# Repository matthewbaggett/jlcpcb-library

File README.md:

JLCPCB Autogenerated parts library
==================================

JLCPCB kindly provides a nice spreadsheet of parts available for their PCBA service.

I thought it'd be useful to turn that into an eaglecad parts library.

To maximise its usefulness, I've done a few other things:

 * Copied Sparkfuns fabulous Power Symbols library
 * Copied CAM job, Desirn Rules file & ULPs from https://github.com/oxullo/jlcpcb-eagle
 
## TODO List:
 * Fix non-trivial packages (multipin ICs)
 * Write Guide on how to export for JLCPCB:
   * Layout guidelines
   * Part picking
   * CAM exporting
   * Running jlcpcb_smta_exporter.ulp to get BOM and placement.
 * Dockerise this tool
 * Create github actions to run on a schedule.
 * Add github actions linting.
 * Proceedurally generate power symbols from a list of power rails

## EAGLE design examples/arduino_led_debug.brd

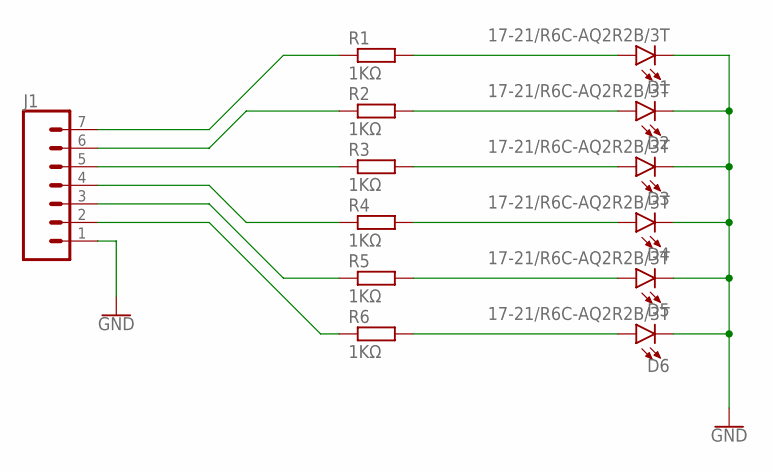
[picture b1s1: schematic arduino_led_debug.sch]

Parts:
D1, D2, D3, D4, D5, D6: 17-21/R6C-AQ2R2B/3T; LED_0805
J1: CONN_07LOCK; 1X07_LOCK
R1, R2, R3, R4, R5, R6: 1KΩ; RESISTOR_0402

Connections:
GND: D1.C, D2.C, D3.C, D4.C, D5.C, D6.C, J1.1
unnamed: D1.A, R1.1 (2)
unnamed: D2.A, R2.1 (2)
unnamed: D3.A, R3.1 (2)
unnamed: J1.7, R1.2 (1)
unnamed: D4.A, R4.1 (2)
unnamed: J1.2, R6.2 (1)
unnamed: J1.3, R5.2 (1)
unnamed: J1.4, R4.2 (1)
unnamed: J1.5, R3.2 (1)
unnamed: J1.6, R2.2 (1)
unnamed: D5.A, R5.1 (2)
unnamed: D6.A, R6.1 (2)

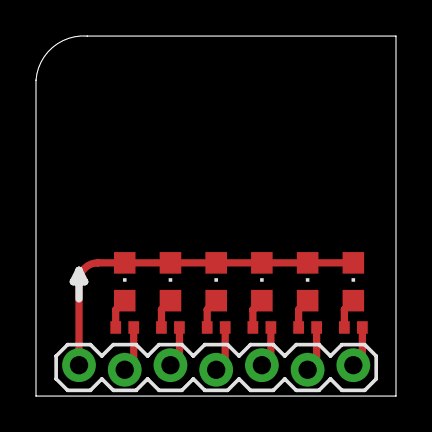
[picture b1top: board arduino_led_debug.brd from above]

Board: 2 copper layers, 20.0 x 20.0 mm, 13 parts (0 on the bottom side), 13 nets.

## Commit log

2020-03-31 Initial commit - Reads in the jlcpcb spreadsheet.
2020-04-05 Progress so far
2020-04-05 Fix up deps.
2020-04-05 First loadable libraries.
2020-04-05 More loadable libraries.
2020-04-05 Add more packages.
2020-04-05 More items.
2020-04-05 More parts. More documentation.
2020-04-10 Copied in some assets.
2020-04-10 Adding the skeleton of an example board project.
2020-04-11 Improving library. Still no real LED library! Added example project to test ULPs against.
2020-04-12 Shrank the label mess for 0402 - No value, just name.
2020-04-13 Updated Pins and Grid data.
2020-04-13 SM4007PL
2020-04-13 Working CH340g, but not programatically :thinking:
2020-04-13 IC_CH340G bits
2020-04-13 Device name strategy change.
2020-04-13 Now generates wonkey ICs
2020-04-13 rename
2020-10-13 Revise 0402 cap
2020-10-13 Minor parts changes
2020-10-13 Temporarilly supress a warning
2020-10-13 Add interop polyfills and updates
2020-10-15 Fix device set name generation. Regenerated libraries.
2021-06-29 Bump league/flysystem from 1.0.66 to 1.1.4
    Bumps [league/flysystem](https://github.com/thephpleague/flysystem) from 1.0.66 to 1.1.4.
    - [Release notes](https://github.com/thephpleague/flysystem/releases)
    - [Changelog](https://github.com/thephpleague/flysystem/blob/2.x/CHANGELOG.md)
    - [Commits](https://github.com/thephpleague/flysystem/compare/1.0.66...1.1.4)
    ---
    updated-dependencies:
2022-05-25 Bump guzzlehttp/guzzle from 6.5.2 to 6.5.6
    Bumps [guzzlehttp/guzzle](https://github.com/guzzle/guzzle) from 6.5.2 to 6.5.6.
    - [Release notes](https://github.com/guzzle/guzzle/releases)
    - [Changelog](https://github.com/guzzle/guzzle/blob/6.5.6/CHANGELOG.md)
    - [Commits](https://github.com/guzzle/guzzle/compare/6.5.2...6.5.6)
    ---
    updated-dependencies:
2022-06-10 Bump guzzlehttp/guzzle from 6.5.2 to 6.5.7
    Bumps [guzzlehttp/guzzle](https://github.com/guzzle/guzzle) from 6.5.2 to 6.5.7.
    - [Release notes](https://github.com/guzzle/guzzle/releases)
    - [Changelog](https://github.com/guzzle/guzzle/blob/6.5.7/CHANGELOG.md)
    - [Commits](https://github.com/guzzle/guzzle/compare/6.5.2...6.5.7)
    ---
    updated-dependencies:
2022-06-21 Bump guzzlehttp/guzzle from 6.5.2 to 6.5.8
    Bumps [guzzlehttp/guzzle](https://github.com/guzzle/guzzle) from 6.5.2 to 6.5.8.
    - [Release notes](https://github.com/guzzle/guzzle/releases)
    - [Changelog](https://github.com/guzzle/guzzle/blob/6.5.8/CHANGELOG.md)
    - [Commits](https://github.com/guzzle/guzzle/compare/6.5.2...6.5.8)
    ---
    updated-dependencies:

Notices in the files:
parts and their libraries:
SparkFun-Connectors: Licensing: Creative Commons ShareAlike 4.0 International - https://creativecommons.org/licenses/by-sa/4.0
Power Symbols: Licensing: Creative Commons ShareAlike 4.0 International -
https://creativecommons.org/licenses/by-sa/4.0
